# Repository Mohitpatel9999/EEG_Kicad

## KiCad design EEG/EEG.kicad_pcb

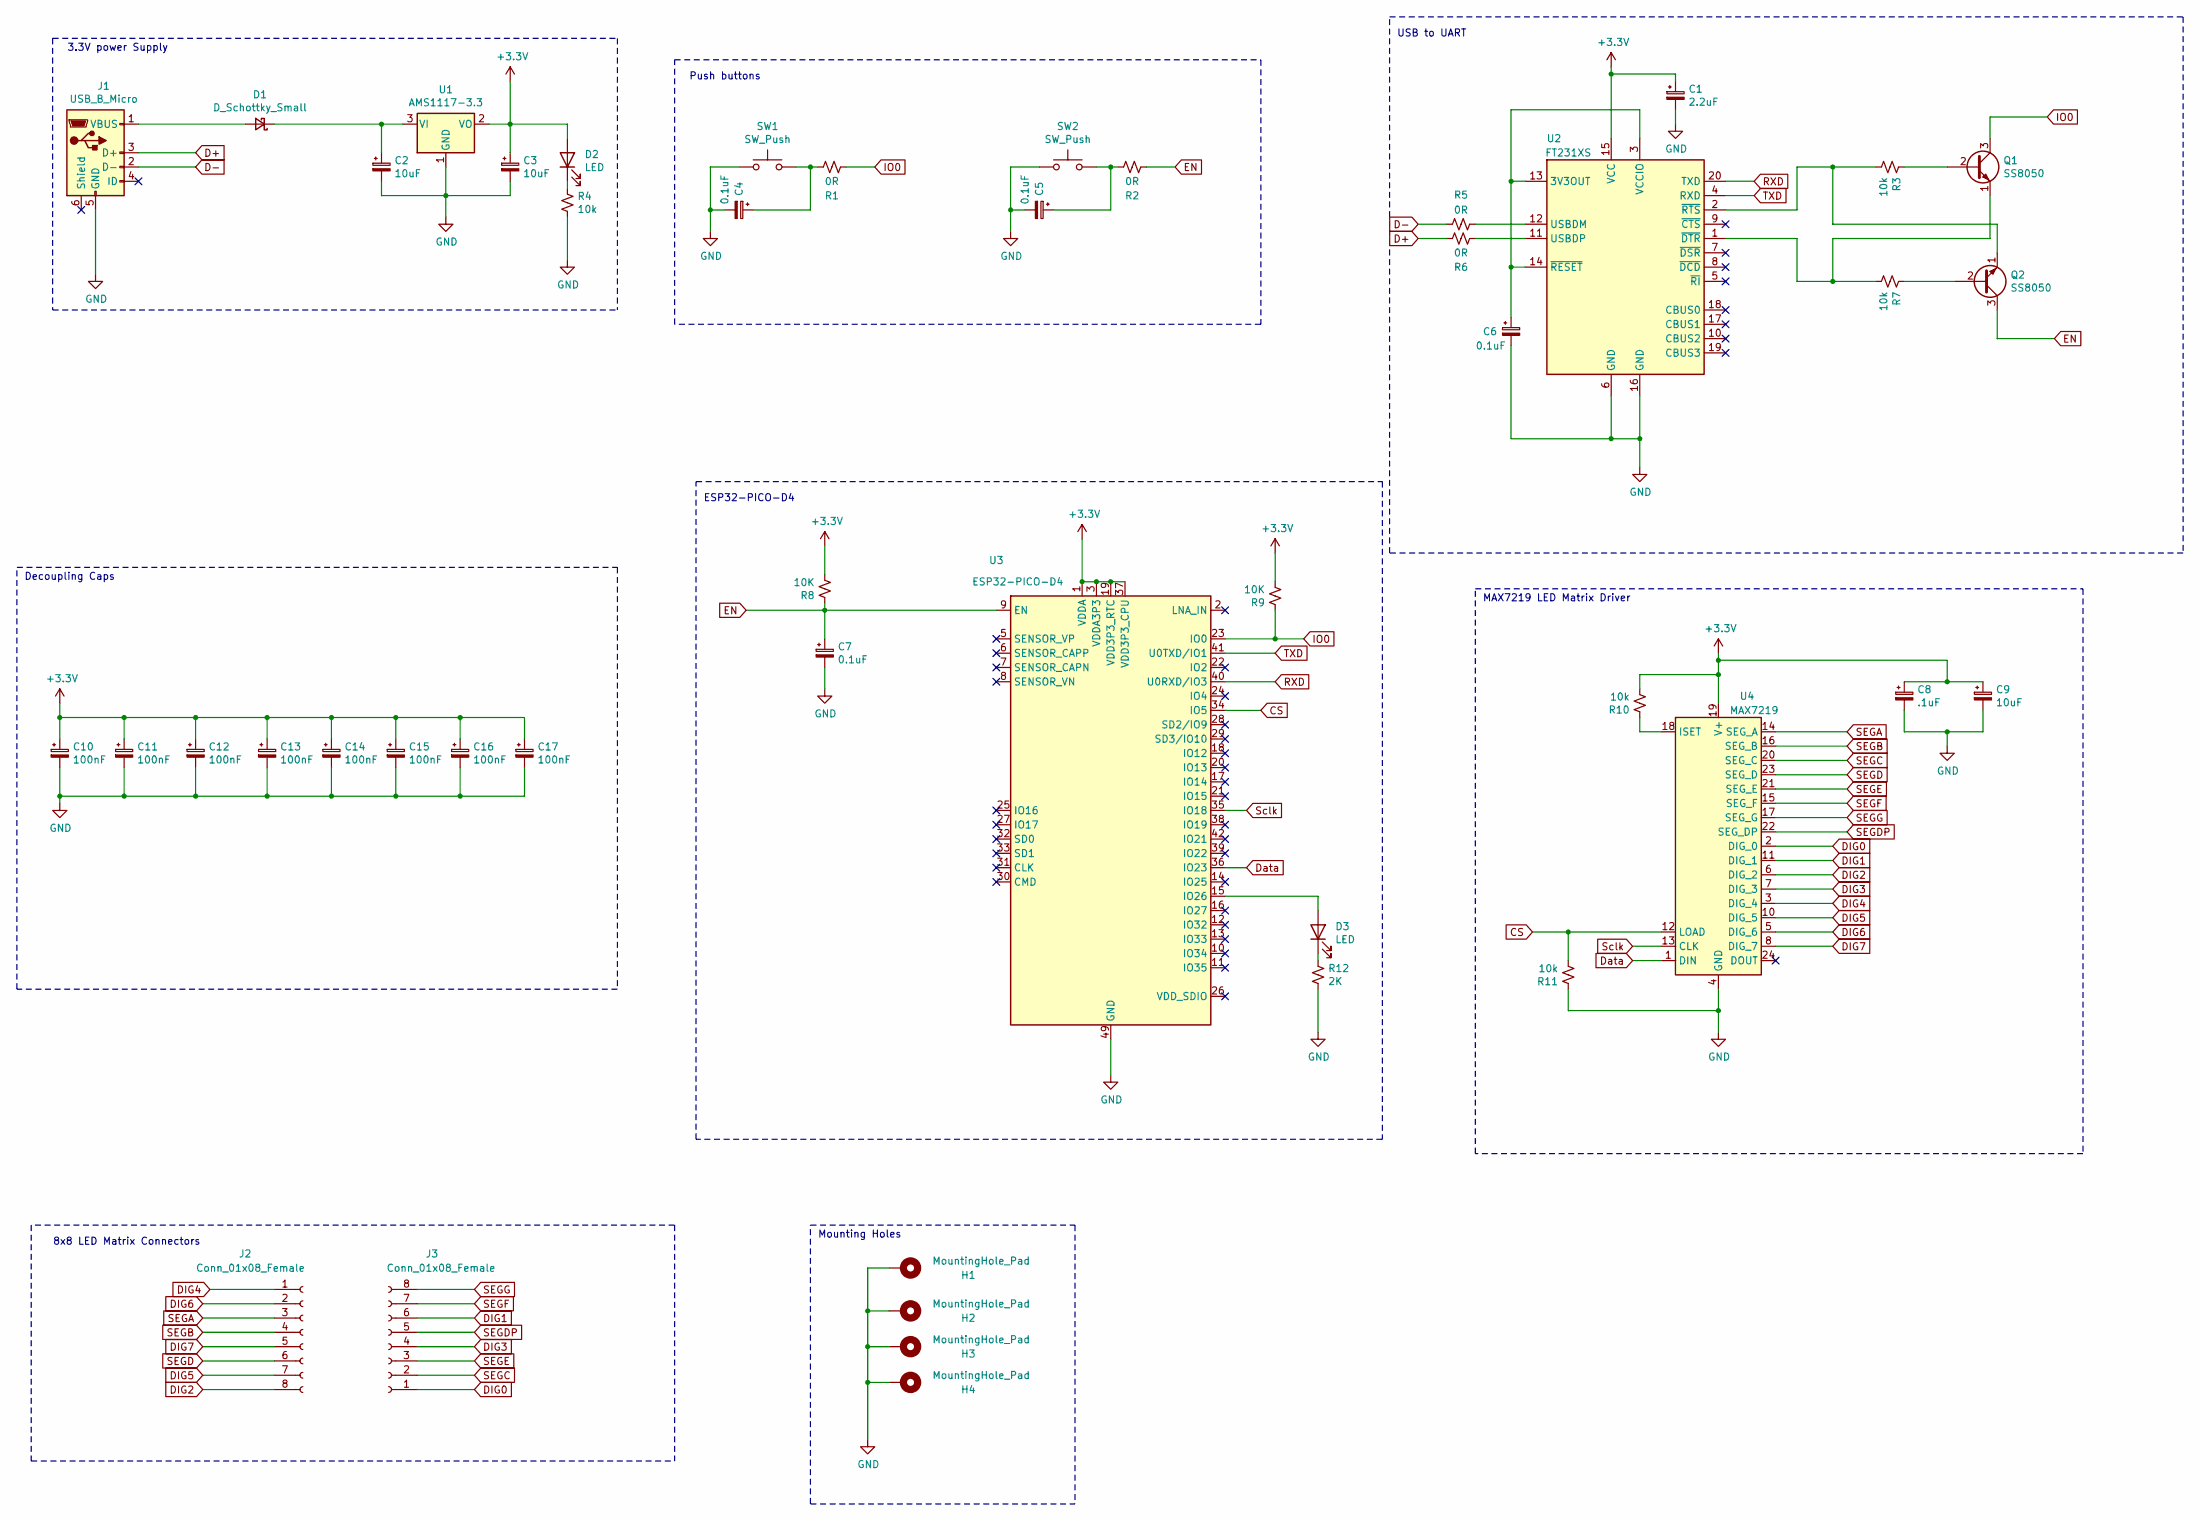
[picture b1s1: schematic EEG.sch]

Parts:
C1: 2.2uF; C_1206_3216Metric_Pad1.33x1.80mm_HandSolder
C2, C3, C9: 10uF; C_1206_3216Metric_Pad1.33x1.80mm_HandSolder
C4, C5, C6, C7: 0.1uF; C_1206_3216Metric_Pad1.33x1.80mm_HandSolder
C8: .1uF; C_1206_3216Metric_Pad1.33x1.80mm_HandSolder
C10, C11, C12, C13, C14, C15, C16, C17: 100nF; C_1206_3216Metric_Pad1.33x1.80mm_HandSolder
D1: D_Schottky_Small; D_1206_3216Metric_Pad1.42x1.75mm_HandSolder
D2, D3: LED; LED_1206_3216Metric_Pad1.42x1.75mm_HandSolder
H1, H2, H3, H4: MountingHole_Pad; MountingHole_4.3mm_M4_Pad_Via
J1: USB_B_Micro; USB_Micro-B_Molex-105017-0001
J2, J3: Conn_01x08_Female; PinSocket_1x08_P2.54mm_Vertical
Q1, Q2: SS8050; SOT-23
R1, R2, R5, R6: 0R; R_1206_3216Metric_Pad1.30x1.75mm_HandSolder
R3, R4, R7, R10, R11: 10k; R_1206_3216Metric_Pad1.30x1.75mm_HandSolder
R8, R9: 10K; R_1206_3216Metric_Pad1.30x1.75mm_HandSolder
R12: 2K; R_1206_3216Metric_Pad1.30x1.75mm_HandSolder
SW1, SW2: SW_Push; SW_Push_1P1T-SH_NO_CK_KMR2xxG
U1: AMS1117-3.3; SOT-223-3_TabPin2
U2: FT231XS; SSOP-20_3.9x8.7mm_P0.635mm
U3: ESP32-PICO-D4; QFN-48-1EP_7x7mm_P0.5mm_EP5.3x5.3mm
U4: MAX7219; SOIC24

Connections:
+3V3: C1.1, C3.1, C8.1, C9.1, C10.1, C11.1, C12.1, C13.1, C14.1, C15.1, C16.1, C17.1, D2.2 (A), R8.2, R9.2, R10.2, U1.2 (VO), U2.15 (VCC), U3.1 (VDDA), U3.3 (VDDA3P3), U3.4 (VDDA3P3), U3.19 (VDD3P3_RTC), U3.37 (VDD3P3_CPU), U3.43 (VDDA), U3.46 (VDDA), U4.19 (V+); also elsewhere on the board
CS: R11.2, U3.34 (IO5), U4.12 (LOAD)
D+: J1.3 (D+), R6.2
D-: J1.2 (D-), R5.2
DIG0: J3.1, U4.2 (DIG_0)
DIG1: J3.6, U4.11 (DIG_1)
DIG2: J2.8, U4.6 (DIG_2)
DIG3: J3.4, U4.7 (DIG_3)
DIG4: J2.1, U4.3 (DIG_4)
DIG5: J2.7, U4.10 (DIG_5)
DIG6: J2.2, U4.5 (DIG_6)
DIG7: J2.5, U4.8 (DIG_7)
Data: U3.36 (IO23), U4.1 (DIN)
EN: C7.1, Q2.3 (C), R2.1, R8.1, U3.9 (EN)
GND: C1.2, C2.2, C3.2, C4.2, C5.2, C6.2, C7.2, C8.2, C9.2, C10.2, C11.2, C12.2, C13.2, C14.2, C15.2, C16.2, C17.2, H1.1, H2.1, H3.1, H4.1, J1.5 (GND), R4.2, R11.1, R12.2, SW1.1, SW2.1, U1.1 (GND), U2.6 (GND), U2.16 (GND), U3.49 (GND), U4.4 (GND), U4.9 (GND)
IO0: Q1.3 (C), R1.1, R9.1, U3.23 (IO0)
unnamed: C2.1, D1.1 (K), U1.3 (VI)
unnamed: C4.1, R1.2, SW1.2
unnamed: C5.1, R2.2, SW2.2
unnamed: C6.1, U2.3 (VCCIO), U2.13 (3V3OUT), U2.14 (~RESET)
unnamed: D1.2 (A), J1.1 (VBUS)
unnamed 21: D2.1 (K), R4.1; also elsewhere on the board
unnamed 22: D3.1 (K), R12.1; also elsewhere on the board
unnamed 23: D3.2 (A), U3.15 (IO26); also elsewhere on the board
unnamed: Q1.1 (E), R7.2, U2.1 (~DTR)
unnamed: Q1.2 (B), R3.1
unnamed: Q2.1 (E), R3.2, U2.2 (~RTS)
unnamed: Q2.2 (B), R7.1
unnamed: R5.1, U2.12 (USBDM)
unnamed: R6.1, U2.11 (USBDP)
unnamed: R10.1, U4.18 (ISET)
RXD: U2.20 (TXD), U3.40 (U0RXD/IO3)
SEGA: J2.3, U4.14 (SEG_A)
SEGB: J2.4, U4.16 (SEG_B)
SEGC: J3.2, U4.20 (SEG_C)
SEGD: J2.6, U4.23 (SEG_D)
SEGDP: J3.5, U4.22 (SEG_DP)
SEGE: J3.3, U4.21 (SEG_E)
SEGF: J3.7, U4.15 (SEG_F)
SEGG: J3.8, U4.17 (SEG_G)
Sclk: U3.35 (IO18), U4.13 (CLK)
TXD: U2.4 (RXD), U3.41 (U0TXD/IO1)

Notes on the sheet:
3.3V power Supply
USB to UART
Push buttons
Mounting Holes
Decoupling Caps
ESP32-PICO-D4
MAX7219 LED Matrix Driver
8x8 LED Matrix Connectors

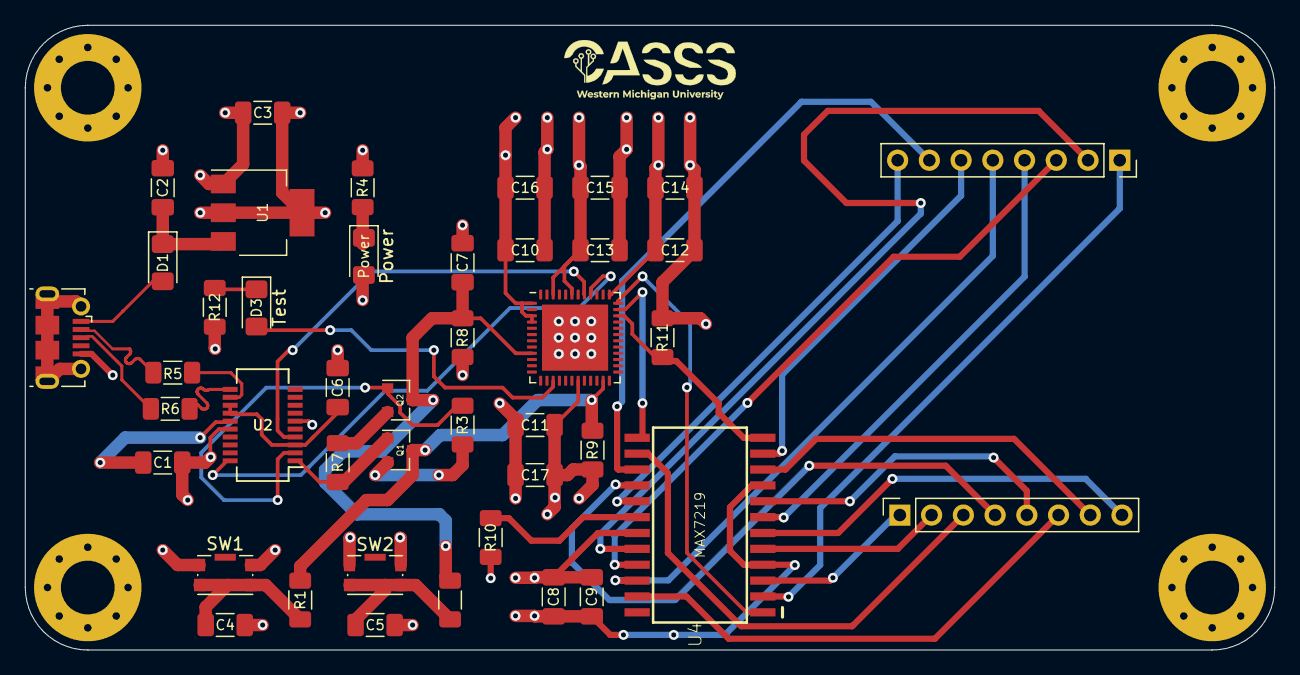
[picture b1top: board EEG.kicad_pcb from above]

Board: 4 copper layers, 100.0 x 50.0 mm, 47 parts (0 on the bottom side), 42 nets.

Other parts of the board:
Power: LED; LED_1206_3216Metric_Pad1.42x1.75mm_HandSolder
Test: LED; LED_1206_3216Metric_Pad1.42x1.75mm_HandSolder

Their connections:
+3V3: Power.2; also elsewhere on the board
unnamed 21: Power.1; also elsewhere on the board
unnamed 22: Test.1; also elsewhere on the board
unnamed 23: Test.2; also elsewhere on the board

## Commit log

2021-03-07 added stuff to schematic
2021-03-09 ADDED LED
2021-03-10 added some footprints
2021-03-10 need to add max7219 footprint
2021-03-12 added some pcb layout
2021-03-14 updated sch for led conn
2021-03-15 added some route
2021-03-15 added more trace
2021-03-16 Finished routing
2021-03-16 addded png
2021-03-17 just BOM and gerbers left
2021-03-17 updated pics
2021-03-29 generated gerbers
2021-04-01 Added picture
2021-04-01 Added schematic pdf
2021-04-01 added BOM
2021-04-21 added picture of the assembled board,
2021-04-21 assembled pcb
